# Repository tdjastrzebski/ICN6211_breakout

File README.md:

# ICN6211 MIPI DSI to RGB LCD Breakout

This is a breakout for ICN6211 MIPI DSI Bridge to RGB output.

The DSI connector is a 20 pin 1mm pitch designed to be used together with the STM32MP157A-DK1 board.

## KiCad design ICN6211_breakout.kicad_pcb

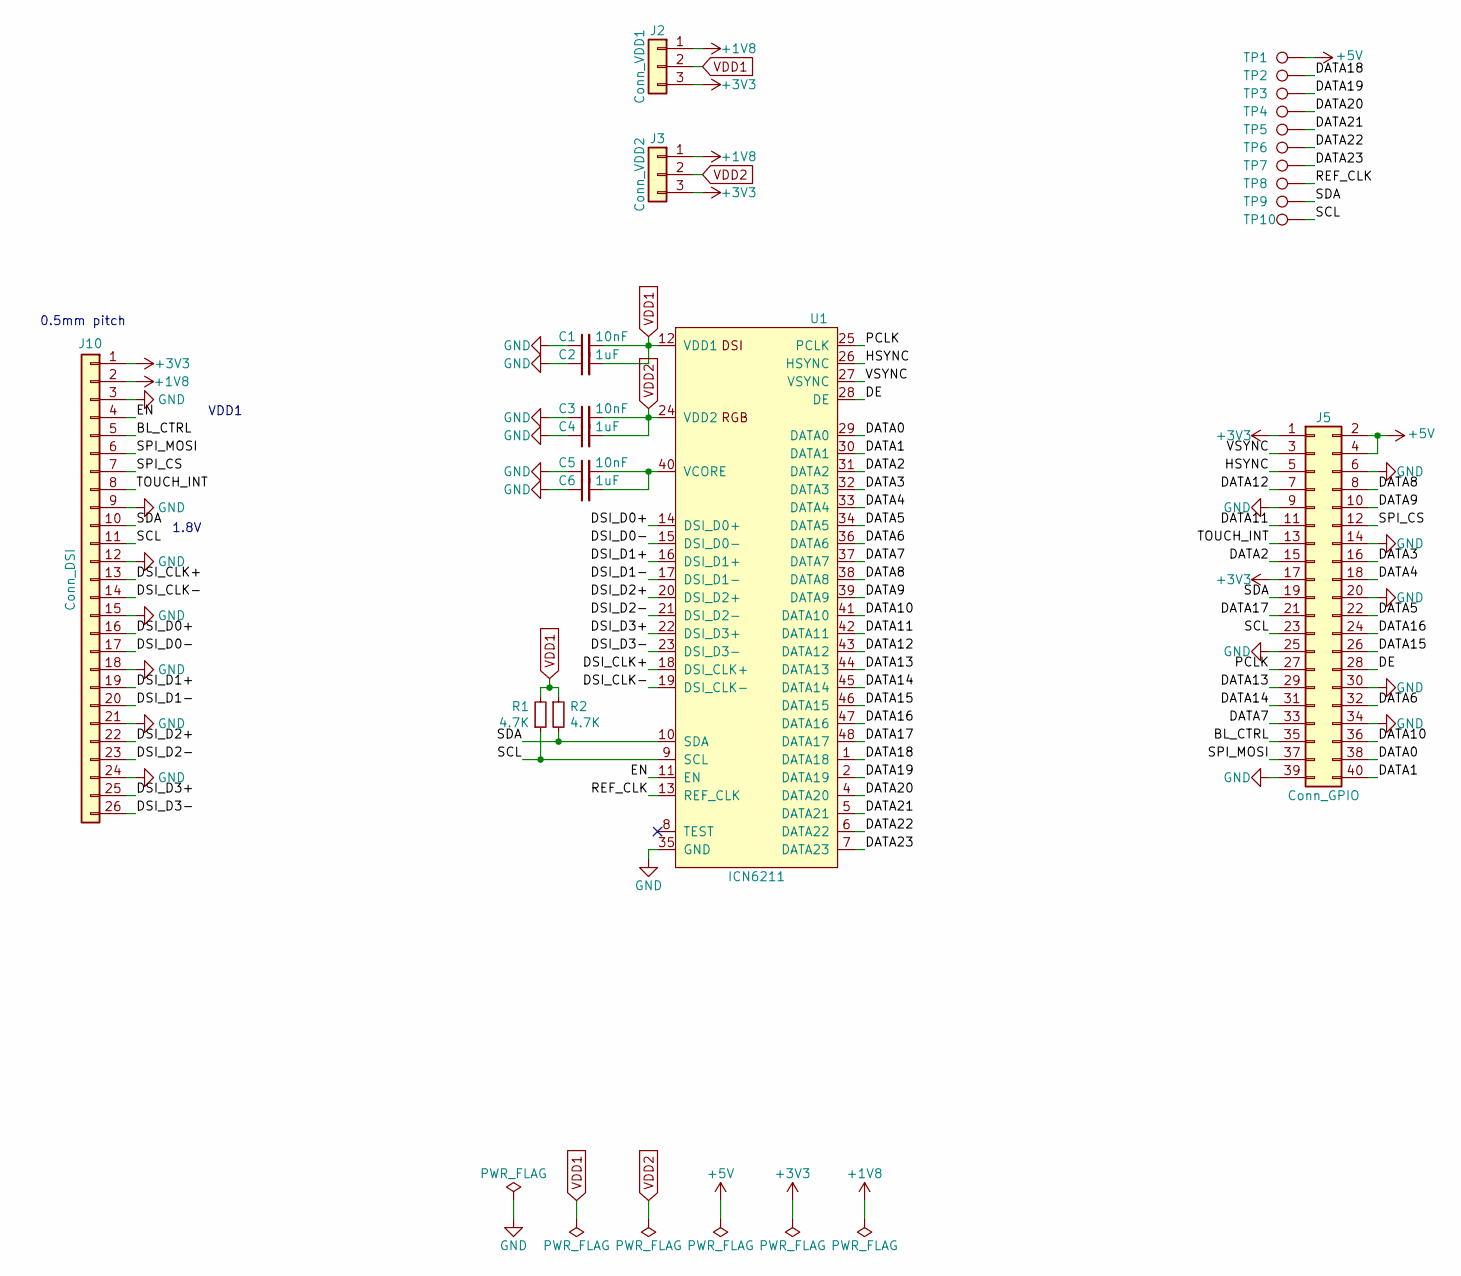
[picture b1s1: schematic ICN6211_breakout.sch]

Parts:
C1, C3, C5: 10nF; C_0603_1608Metric
C2, C4, C6: 1uF; C_0603_1608Metric
J2: Conn_VDD1; PinHeader_1x03_P2.54mm_Vertical
J3: Conn_VDD2; PinHeader_1x03_P2.54mm_Vertical
J5: Conn_GPIO; PinHeader_2x20_P2.54mm_Vertical
J10: Conn_DSI; TE_2-1734839-6_1x26-1MP_P0.5mm_Horizontal
R1, R2: 4.7K; R_0603_1608Metric
TP1: TP_5V; TestPoint_Pad_D1.0mm
TP2: TP_DATA18; TestPoint_Pad_D1.0mm
TP3: TP_DATA19; TestPoint_Pad_D1.0mm
TP4: TP_DATA20; TestPoint_Pad_D1.0mm
TP5: TP_DATA21; TestPoint_Pad_D1.0mm
TP6: TP_DATA22; TestPoint_Pad_D1.0mm
TP7: TP_DATA23; TestPoint_Pad_D1.0mm
TP8: TP_REF_CLK; TestPoint_Pad_D1.0mm
TP9: TP_SDA; TestPoint_Pad_D1.0mm
TP10: TP_SCL; TestPoint_Pad_D1.0mm
U1: ICN6211; QFN-48-1EP_6x6mm_P0.4mm_EP4.2x4.2mm

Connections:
+1V8: J2.1, J3.1, J10.2
+3V3: J2.3, J3.3, J5.1, J5.17, J10.1
+5V: J5.2, J5.4, TP1.1
/BL_CTRL: J5.35, J10.5
/DATA0: J5.38, U1.29 (DATA0)
/DATA1: J5.40, U1.30 (DATA1)
/DATA2: J5.15, U1.31 (DATA2)
/DATA3: J5.16, U1.32 (DATA3)
/DATA4: J5.18, U1.33 (DATA4)
/DATA5: J5.22, U1.34 (DATA5)
/DATA6: J5.32, U1.36 (DATA6)
/DATA7: J5.33, U1.37 (DATA7)
/DATA8: J5.8, U1.38 (DATA8)
/DATA9: J5.10, U1.39 (DATA9)
/DATA10: J5.36, U1.41 (DATA10)
/DATA11: J5.11, U1.42 (DATA11)
/DATA12: J5.7, U1.43 (DATA12)
/DATA13: J5.29, U1.44 (DATA13)
/DATA14: J5.31, U1.45 (DATA14)
/DATA15: J5.26, U1.46 (DATA15)
/DATA16: J5.24, U1.47 (DATA16)
/DATA17: J5.21, U1.48 (DATA17)
/DATA18: TP2.1, U1.1 (DATA18)
/DATA19: TP3.1, U1.2 (DATA19)
/DATA20: TP4.1, U1.4 (DATA20)
/DATA21: TP5.1, U1.5 (DATA21)
/DATA22: TP6.1, U1.6 (DATA22)
/DATA23: TP7.1, U1.7 (DATA23)
/DE: J5.28, U1.28 (DE)
/DSI_CLK+: J10.13, U1.18 (DSI_CLK+)
/DSI_CLK-: J10.14, U1.19 (DSI_CLK-)
/DSI_D0+: J10.16, U1.14 (DSI_D0+)
/DSI_D0-: J10.17, U1.15 (DSI_D0-)
/DSI_D1+: J10.19, U1.16 (DSI_D1+)
/DSI_D1-: J10.20, U1.17 (DSI_D1-)
/DSI_D2+: J10.22, U1.20 (DSI_D2+)
/DSI_D2-: J10.23, U1.21 (DSI_D2-)
/DSI_D3+: J10.25, U1.22 (DSI_D3+)
/DSI_D3-: J10.26, U1.23 (DSI_D3-)
/EN: J10.4, U1.11 (EN)
/HSYNC: J5.5, U1.26 (HSYNC)
/PCLK: J5.27, U1.25 (PCLK)
/REF_CLK: TP8.1, U1.13 (REF_CLK)
/SCL: J5.23, J10.11, R1.1, TP10.1, U1.9 (SCL)
/SDA: J5.19, J10.10, R2.2, TP9.1, U1.10 (SDA)
/SPI_CS: J5.12, J10.7
/SPI_MOSI: J5.37, J10.6
/TOUCH_INT: J5.13, J10.8
/VSYNC: J5.3, U1.27 (VSYNC)
GND: C1.1, C2.1, C3.1, C4.1, C5.1, C6.1, J5.6, J5.9, J5.14, J5.20, J5.25, J5.30, J5.34, J5.39, J10.3, J10.9, J10.12, J10.15, J10.18, J10.21, J10.24, U1.35 (GND), U1.49 (PAD)
unnamed: C5.2, C6.2, U1.40 (VCORE)
VDD1: C1.2, C2.2, J2.2, R1.2, R2.1, U1.12 (VDD1)
VDD2: C3.2, C4.2, J3.2, U1.3 (VDD3), U1.24 (VDD2)

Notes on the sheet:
0.5mm pitch
1.8V
VDD1

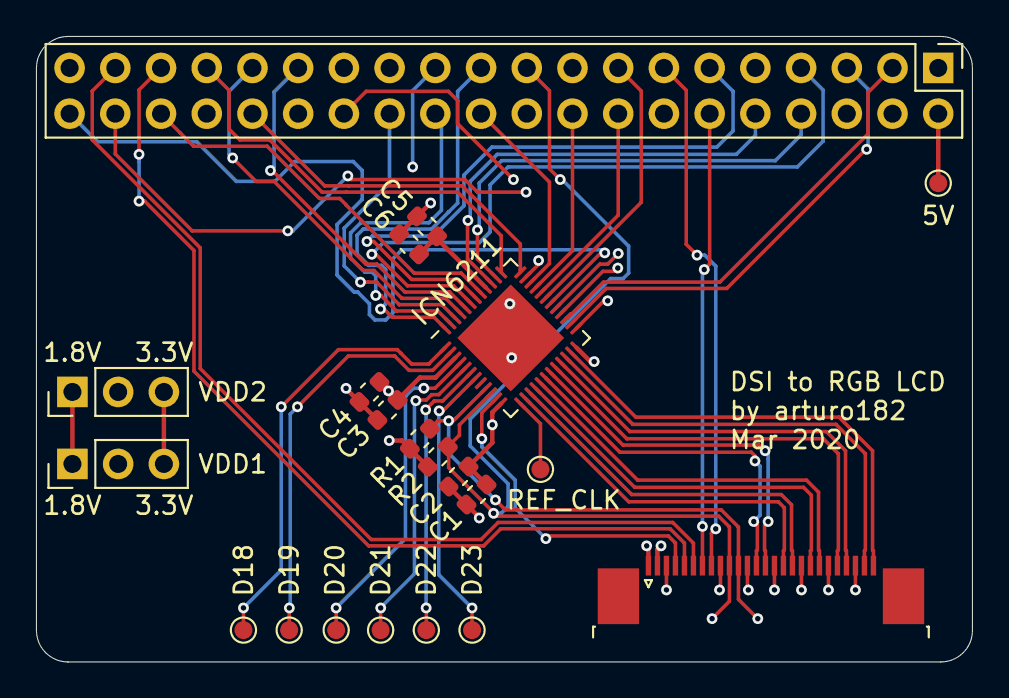
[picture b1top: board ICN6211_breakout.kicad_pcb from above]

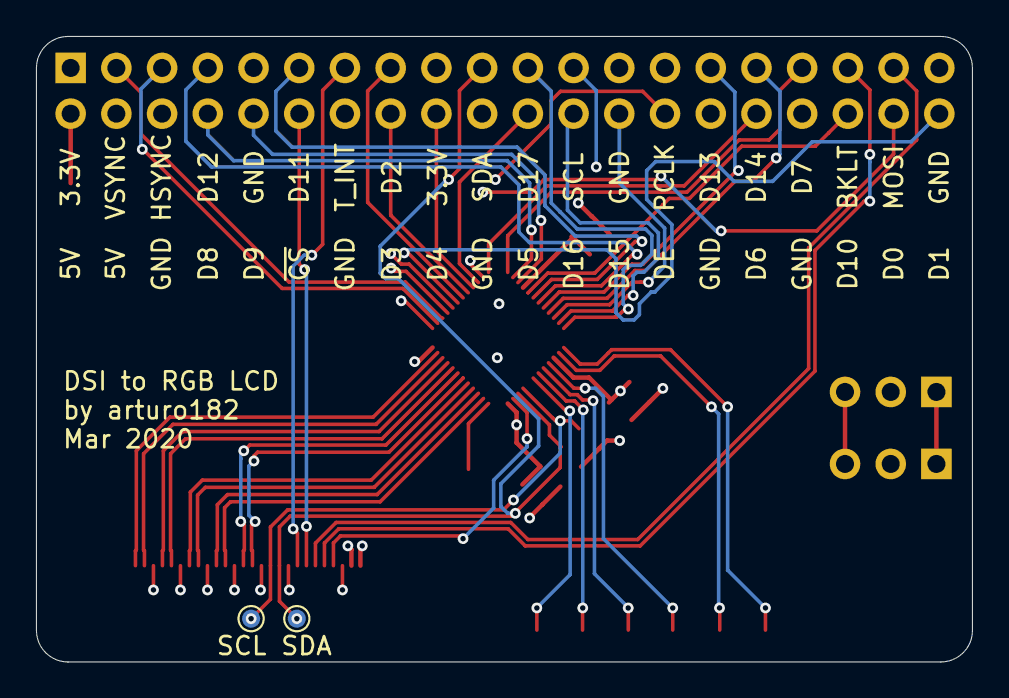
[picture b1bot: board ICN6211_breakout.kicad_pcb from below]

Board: 4 copper layers, 52.0 x 34.8 mm, 23 parts (2 on the bottom side), 53 nets.

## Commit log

2020-02-23 Initial import
2020-03-24 Rev 2
